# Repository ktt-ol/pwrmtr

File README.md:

This PCB can be used to read out data from smart meters commonly found in
Germany using their IR interface. It's intended to be used with 3.3V or 5V
serial interfaces, for example with USB UART-TTL adapters (e.g. from FTDI)
or microcontrollers such as the ESP8266 or ESP32 series.

# Schematic

# Pictures

# Software

For initial testing a USB UART-TTL adapter is quite useful. It can be used
to directly check the smart meter output with a laptop. Note that some meters
use a binary protocol called [SML](https://de.wikipedia.org/wiki/Smart_Message_Language)
(Smart Message Language). On Debian `sml_server` (from
[libsml-utils](https://packages.debian.org/trixie/libsml-utils) package) can be
used to decode it.

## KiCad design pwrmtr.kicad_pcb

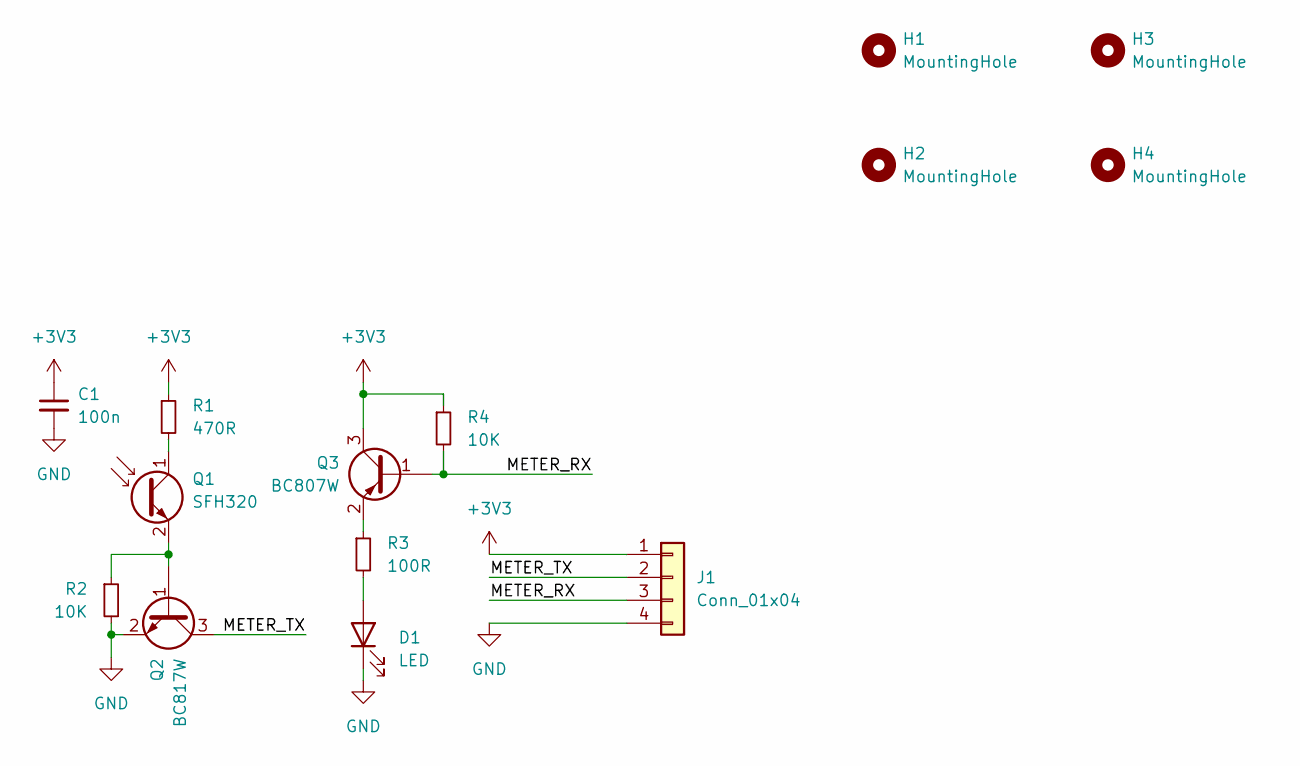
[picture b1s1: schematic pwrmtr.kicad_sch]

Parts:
C1: 100n; C_0603_1608Metric
D1: LED; D_0603_1608Metric
H1, H2, H3, H4: MountingHole; MountingHole_3.2mm_M3
J1: Conn_01x04; PinHeader_1x04_P2.54mm_Horizontal
Q1: SFH320; LED_PLCC-2_3.4x3.0mm_KA
Q2: BC817W; SOT-323_SC-70
Q3: BC807W; SOT-323_SC-70
R1: 470R; R_0603_1608Metric
R2, R4: 10K; R_0603_1608Metric
R3: 100R; R_0603_1608Metric

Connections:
+3V3: C1.1, J1.1, Q3.3 (C), R1.1, R4.1
/METER_RX: J1.3, Q3.1 (B), R4.2
/METER_TX: J1.2, Q2.3 (C)
GND: C1.2, D1.1 (K), J1.4, Q2.2 (E), R2.2
unnamed: D1.2 (A), R3.2
unnamed: Q1.1 (C), R1.2
unnamed: Q1.2 (E), Q2.1 (B), R2.1
unnamed: Q3.2 (E), R3.1

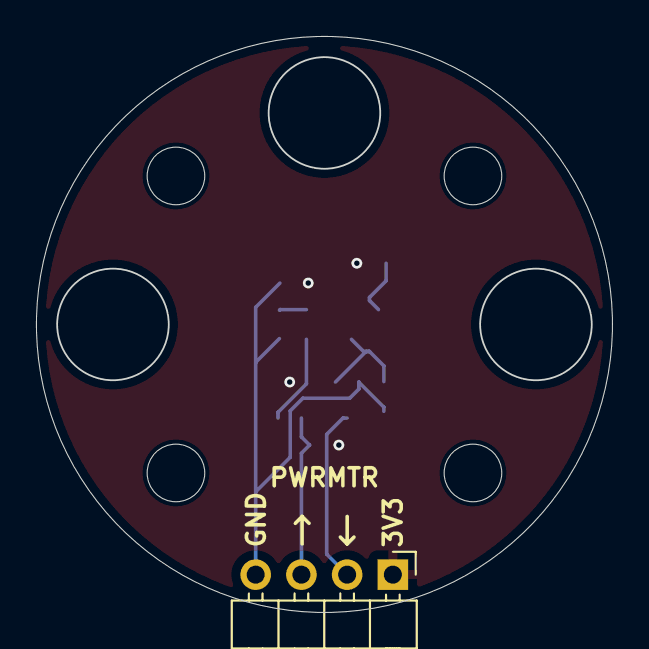
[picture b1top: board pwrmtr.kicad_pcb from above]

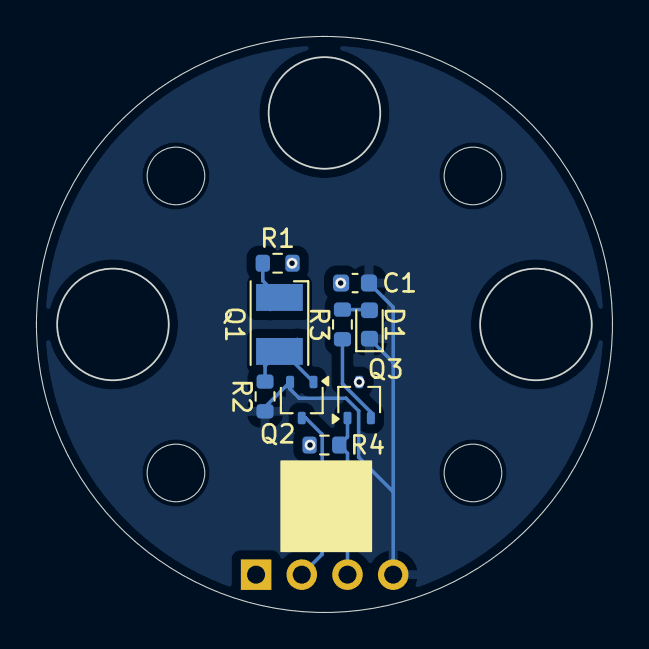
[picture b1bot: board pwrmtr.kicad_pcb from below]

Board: 2 copper layers, 32.0 x 32.0 mm, 14 parts (9 on the bottom side), 8 nets.
